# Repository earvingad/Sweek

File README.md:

# Sweek
Sweek is a Ferris/sweep inspired, 36 keys split keyboard.

The K in the name comes from it using [KMK](https://github.com/KMKfw/kmk_firmware).

It features:
- Reversible PCB with through holes diodes for easy soldering.
- RP2040 as MCU.
- Support for MX, choc V1/V2 and Redragon low profile switches (I only tested MX and Redragon LP).
- EC11 encoders and oled displays.
- Communication is through USB-C (using a pair of small USB-C boards available, since I wanted as easiest to solder as possible).
- There is also a diodeless version.

Please see the [Building guide for v1.0.1](./src/buildingguide_v101.org).

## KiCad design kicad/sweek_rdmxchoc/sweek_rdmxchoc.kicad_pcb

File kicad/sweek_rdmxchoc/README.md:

Please see the [Building guide](https://github.com/earvingad/Sweek/blob/main/src/buildingguide.org).

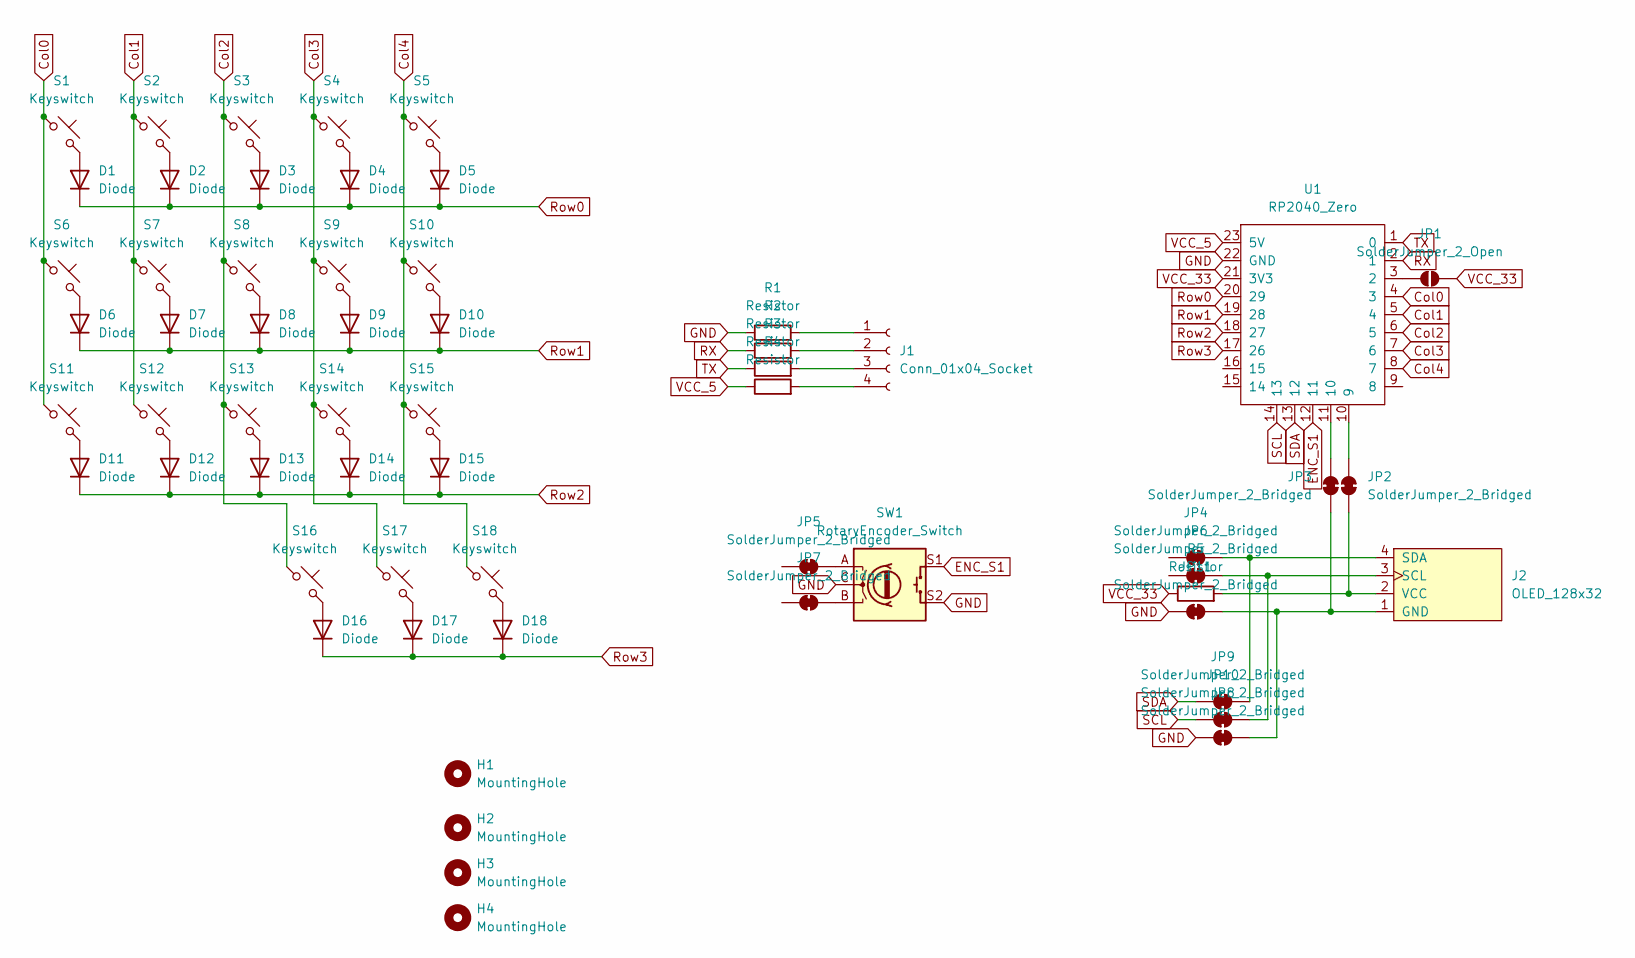
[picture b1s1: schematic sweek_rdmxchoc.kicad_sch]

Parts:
D1, D2, D3, D4, D5, D6, D7, D8, D9, D10, D11, D12, D13, D14, D15, D16, D17, D18: Diode; Diode_DO-35_SOD-123
H1, H2, H3, H4: MountingHole; MountingHole_2.7mm_M2.5
J1: Conn_01x04_Socket; USB_C_board
J2: OLED_128x32
JP1: SolderJumper_2_Open; SolderJumper-2_P1.3mm_Open_TrianglePad1.0x1.5mm_custom
JP2, JP3, JP4, JP5, JP6, JP7, JP9, JP10, JP11: SolderJumper_2_Bridged; SolderJumper-2_P1.3mm_Open_RoundedPad1.0x1.5mm_custom
JP8: SolderJumper_2_Bridged; SolderJumper-2_P1.3mm_Bridged_RoundedPad1.0x1.5mm_custom
R1, R2, R3, R4, R5: Resistor; R_1206_3216Metric_Pad1.30x1.75mm_custom
S1, S2, S3, S4, S5, S6, S7, S8, S9, S10, S11, S12, S13, S14, S15, S16, S17, S18: Keyswitch; RD_MX_Choc_V1V2_1.00u
SW1: RotaryEncoder_Switch; RotaryEncoder_Alps_EC11E-Switch_Vertical_H20mm
U1: RP2040_Zero

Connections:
Col0: S1.1, S6.1, S11.1, U1.4 (3)
Col1: S2.1, S7.1, S12.1, U1.5 (4)
Col2: S3.1, S8.1, S13.1, S16.1, U1.6 (5)
Col3: S4.1, S9.1, S14.1, S17.1, U1.7 (6)
Col4: S5.1, S10.1, S15.1, S18.1, U1.8 (7)
ENC_S1: SW1.S1, U1.12 (11)
GND: JP8.2 (B), JP11.2 (B), R1.1, SW1.C, SW1.S2, U1.22 (GND)
unnamed: D1.2 (A), S1.2
unnamed: D2.2 (A), S2.2
unnamed: D3.2 (A), S3.2
unnamed: D4.2 (A), S4.2
unnamed: D5.2 (A), S5.2
unnamed: D6.2 (A), S6.2
unnamed: D7.2 (A), S7.2
unnamed: D8.2 (A), S8.2
unnamed: D9.2 (A), S9.2
unnamed: D10.2 (A), S10.2
unnamed: D11.2 (A), S11.2
unnamed: D12.2 (A), S12.2
unnamed: D13.2 (A), S13.2
unnamed: D14.2 (A), S14.2
unnamed: D15.2 (A), S15.2
unnamed: D16.2 (A), S16.2
unnamed: D17.2 (A), S17.2
unnamed: D18.2 (A), S18.2
unnamed: J1.1, R1.2
unnamed: J1.2, R2.2
unnamed: J1.3, R3.2
unnamed: J1.4, R4.2
unnamed: J2.1 (GND), JP3.1 (A), JP8.1 (A), JP11.1 (A)
unnamed: J2.3 (SCL), JP6.1 (A), JP10.2 (B)
unnamed: J2.4 (SDA), JP4.2 (B), JP9.2 (B)
unnamed: J2.2 (VCC), JP2.1 (A), R5.2
unnamed: JP1.1 (A), U1.3 (2)
unnamed: JP2.2 (B), U1.10 (9)
unnamed: JP3.2 (B), U1.11 (10)
unnamed: JP5.2 (B), SW1.A
unnamed: JP7.2 (B), SW1.B
RX: R2.1, U1.2 (1)
Row0: D1.1 (K), D2.1 (K), D3.1 (K), D4.1 (K), D5.1 (K), U1.20 (29)
Row1: D6.1 (K), D7.1 (K), D8.1 (K), D9.1 (K), D10.1 (K), U1.19 (28)
Row2: D11.1 (K), D12.1 (K), D13.1 (K), D14.1 (K), D15.1 (K), U1.18 (27)
Row3: D16.1 (K), D17.1 (K), D18.1 (K), U1.17 (26)
SCL: JP10.1 (A), U1.14 (13)
SDA: JP9.1 (A), U1.13 (12)
TX: R3.1, U1.1 (0)
VCC_5: R4.1, U1.23 (5V)
VCC_33: JP1.2 (B), R5.1, U1.21 (3V3)

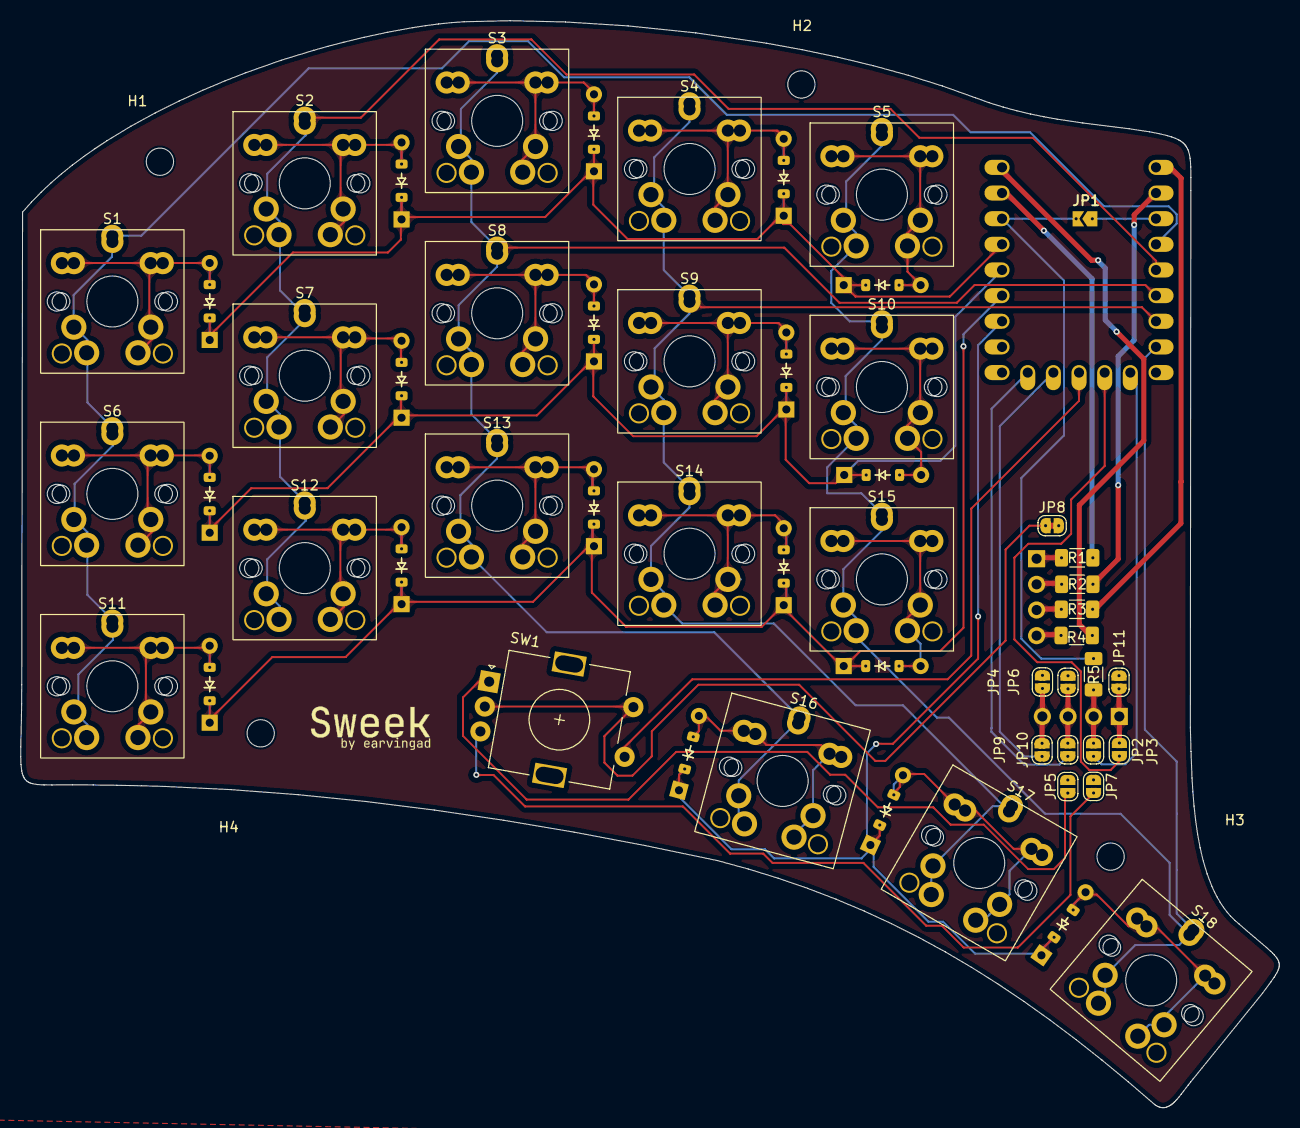
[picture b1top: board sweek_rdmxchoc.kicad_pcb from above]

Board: 2 copper layers, 124.6 x 107.6 mm, 60 parts (1 on the bottom side), 48 nets.

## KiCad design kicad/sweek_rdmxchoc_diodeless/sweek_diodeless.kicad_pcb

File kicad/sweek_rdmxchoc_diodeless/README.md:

Please see the [Building guide](/src/buildingguide_v101.org).

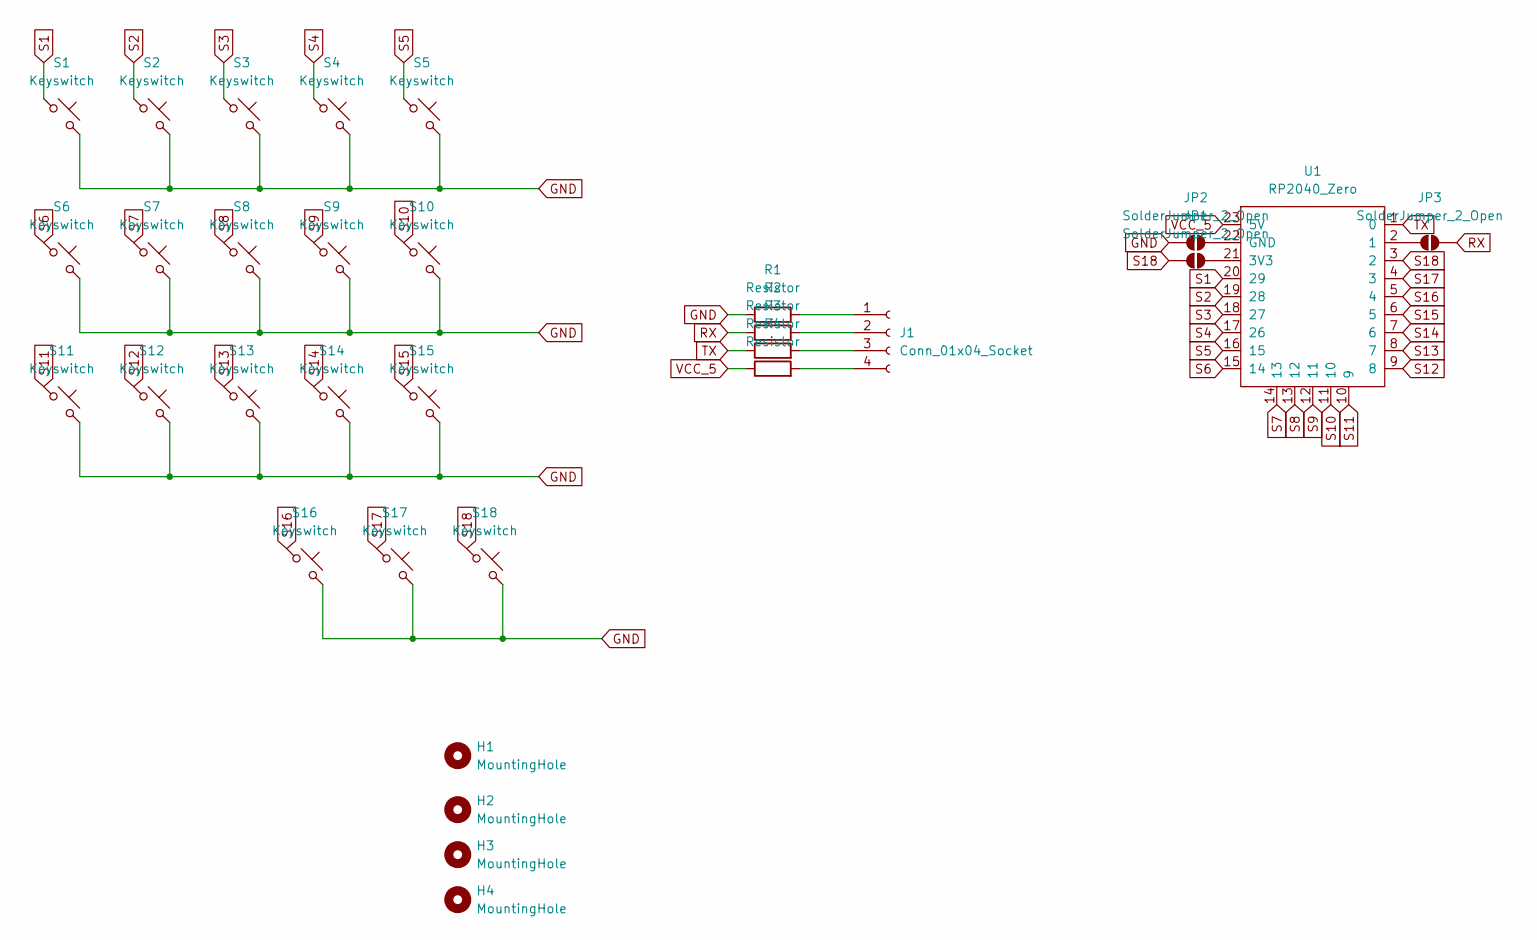
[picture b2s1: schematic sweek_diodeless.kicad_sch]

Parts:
H1, H2, H3, H4: MountingHole; MountingHole_2.7mm_M2.5
J1: Conn_01x04_Socket; USB_C_board
JP1: SolderJumper_2_Open; SolderJumper-2_P1.3mm_Open_TrianglePad1.0x1.5mm_custom
JP2, JP3: SolderJumper_2_Open; SolderJumper-2_P1.3mm_Open_RoundedPad1.0x1.5mm_custom
R1, R2, R3, R4: Resistor; R_1206_3216Metric_Pad1.30x1.75mm_custom
S1, S2, S3, S4, S5, S6, S7, S8, S9, S10, S11, S12, S13, S14, S15, S16, S17, S18: Keyswitch; RD_MX_Choc_V1V2_1.00u
U1: RP2040_Zero

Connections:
GND: JP2.1 (A), R1.1, S1.2, S2.2, S3.2, S4.2, S5.2, S6.2, S7.2, S8.2, S9.2, S10.2, S11.2, S12.2, S13.2, S14.2, S15.2, S16.2, S17.2, S18.2
unnamed: J1.1, R1.2
unnamed: J1.2, R2.2
unnamed: J1.3, R3.2
unnamed: J1.4, R4.2
unnamed: JP1.2 (B), U1.21 (3V3)
unnamed: JP2.2 (B), U1.22 (GND)
unnamed: JP3.1 (A), U1.2 (1)
RX: JP3.2 (B), R2.1
S1: S1.1, U1.20 (29)
S2: S2.1, U1.19 (28)
S3: S3.1, U1.18 (27)
S4: S4.1, U1.17 (26)
S5: S5.1, U1.16 (15)
S6: S6.1, U1.15 (14)
S7: S7.1, U1.14 (13)
S8: S8.1, U1.13 (12)
S9: S9.1, U1.12 (11)
S10: S10.1, U1.11 (10)
S11: S11.1, U1.10 (9)
S12: S12.1, U1.9 (8)
S13: S13.1, U1.8 (7)
S14: S14.1, U1.7 (6)
S15: S15.1, U1.6 (5)
S16: S16.1, U1.5 (4)
S17: S17.1, U1.4 (3)
S18: JP1.1 (A), S18.1, U1.3 (2)
TX: R3.1, U1.1 (0)
VCC_5: R4.1, U1.23 (5V)

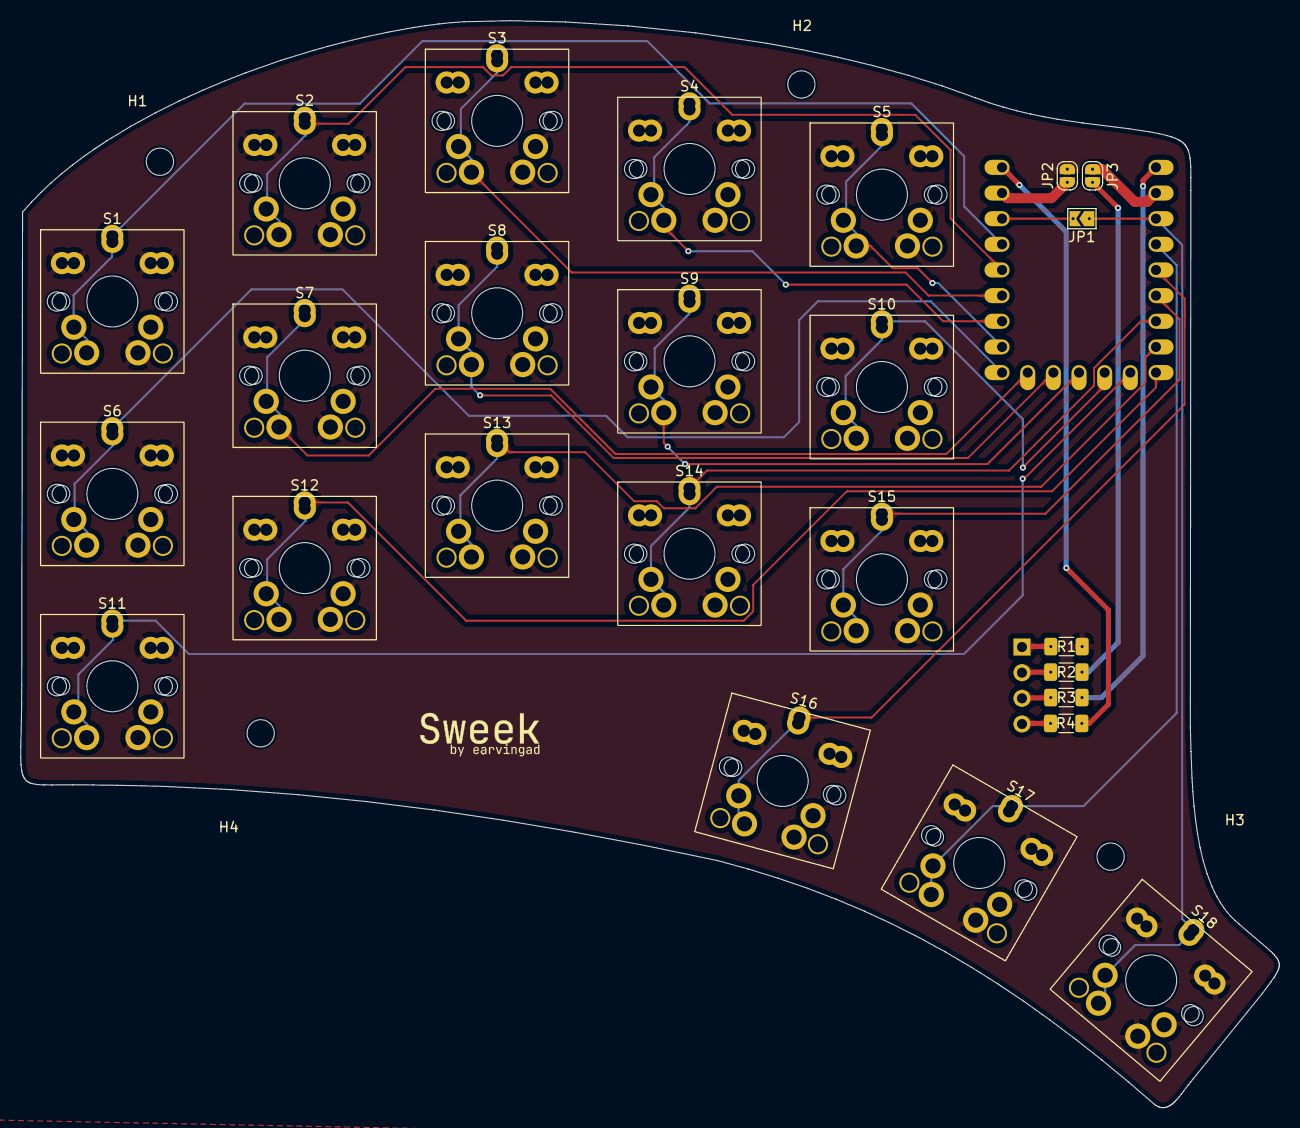
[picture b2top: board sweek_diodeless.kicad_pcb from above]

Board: 2 copper layers, 124.6 x 107.6 mm, 31 parts (0 on the bottom side), 29 nets.

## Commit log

2025-04-14 Sweek svg for laser cut
    Sweek svg for laser cut, made with Inkscape
2025-06-03 Create buildingguide.org
    Added building guide for both sweek versions.
2025-06-03 Upload pictures for guide
    Upload pictures for building guide
2025-06-03 Update buildingguide.org
    Update building guide withe picture references.
2025-06-04 Add diodes reference
    Picture for diodes reference orientation.
2025-06-04 Update buildingguide.org
    Added diode reference information
2025-06-04 kicad files for the sweek
    Original version.
2025-06-04 kicad files sweek diodeless version
    kicad files for the sweek diodeless version
2025-06-04 RD_MX_Choc_V1V2 footprint
    Added RD_MX_Choc_V1V2_1.00u kicad footprint. Supports MX, choc V1/V2 and redragon Low Profile switches.
2025-06-04 Final build example
2025-06-04 Update README.md
    Update readme.
2025-06-04 Update README.md
    Reference to KMK firmware in the name.
2025-06-09 Update kicad original sweek
2025-06-09 Update kicad sweek diodeless
2025-06-09 Create README.md
    Added instructions for KMK files.
2025-06-09 Added code.py for KMK
    Added code.py for KMK firmware
2025-06-09 Update buildingguide.org
    Added EC11 encoder height recommendation.
2025-06-23 Update and rename buildingguide.org to buildingguide_v100.org
    Changing name for building guide for v1.0.0
2025-06-23 Update buildingguide_v100.org
    edit typo in title
2025-06-23 Added reference pictures for building guide v1.0.1
    Added reference pictures for building guide v1.0.1
2025-06-23 Create buildingguide_v101.org
    Added building guide for v1.0.1
2025-06-23 Update buildingguide_v101.org
    Corrected images links
2025-06-23 Update README.md
    update link for building guide v1.0.1
2025-06-23 Update diodeless kicad files for v1.0.1
    Update diodeless kicad files for v1.0.1
2025-06-23 Update sweek kicad files for v1.0.1
    Update sweek kicad files for v1.0.1
2025-06-23 Delete kicad/sweek_rdmxchoc directory
    deletion to correct files wrongly uploaded
2025-06-23 Create README.md
    update readme for sweek v1.0.1
2025-06-23 Update LICENSE
    update licence
2025-06-23 Rename LICENSE to LICENSE.md
2025-06-24 Grammar for building guide v1.0.0
2025-06-25 Correct links in kicad folder.
2026-03-10 Create README.md for RMK firmware
2026-03-17 Update code.py: keymap, modules.
2026-04-01 Create README.md for QMK firmware
2026-04-01 Upload sweek_vial firmware for each half.
2026-04-01 Create README.md for QMK sweek folder
2026-04-01 Upload vial config.h, rules.mk and vial.json
2026-04-01 Upload keyboard level config.h and keyboard.json
2026-04-03 Update README.md QMK
2026-04-04 Update QMK firmware files
2026-04-04 Update README.md Maste left
2026-04-04 Update working vial-QMK files for sweek.
2026-04-05 Update vial.json: to match physical layout.
2026-04-05 Update uf2 files to match vial with physical layout
